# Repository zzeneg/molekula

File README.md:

# molekula: keyboard & framework

## modular framework

This project aims to provide components for building modular ergo keyboards by separating one main PCB into central and side parts. **Side** is a dumb PCB, with key matrix only (up to 25 keys), and accepts all switch types (MX/ChocV1/ChocV2/GLP). **Central** is a keyboard brain, which contains any MCU (wired/wireless/integrated) and additional hardware - encoders/touchpads/trackballs/displays/etc, while keeping its size under 100x100mm. PCBs are interconnected with 12-pin FFC cables, and can be replaced/updated independently.

Such modular approach allows for quick, cheap and easy experimenting with different hardware, prototyping, and reusing of side PCBs.

### PCB examples

- central with pro-micro/nice!nano footprint, nice!view and rotary encoder

- side with 18 keys and minY spacing (19x16mm)

## Molekula keyboards

Reference design using molekula PCBs.

Features:

- minY (19x16mm) spacing
- 36 keys
- wireless
- nice!view support
- rotary encoder

### Molekula2

Unibody that can be disassembled into two parts for traveling

[More info and build guide](./keyboards/Molekula2/README.md)

### Molekula3

Unibody assembled from multiple parts, to allow easy modifications and experiments.

- optimised for FDM printing
- configurable angle and distance between sides (default is 18deg and 60mm)
- different options with dongle or nice!view
- MX/KS-33/ChocV1/ChocV2 are supported, except thumbs are low-profile only

[More info and build guide](./keyboards/Molekula3/README.md)

### minY keycaps

Keycaps designed for minY spacing (19mmx16mm):

- [MX DES](./keycaps/MX-DES-minY/)
- [Choc DES](./keycaps/MX-DES-minY/) - optimised for FDM printing

### Support

If you like my work and want to support my future designs, please consider [sponsorship](https://github.com/sponsors/zzeneg).

### Sponsors

Molekula2 keyboard was sponsored by PCBWay. I can highly recommend their PCBA and 3D printing services - "Imaging Black" resin looks fantastic.

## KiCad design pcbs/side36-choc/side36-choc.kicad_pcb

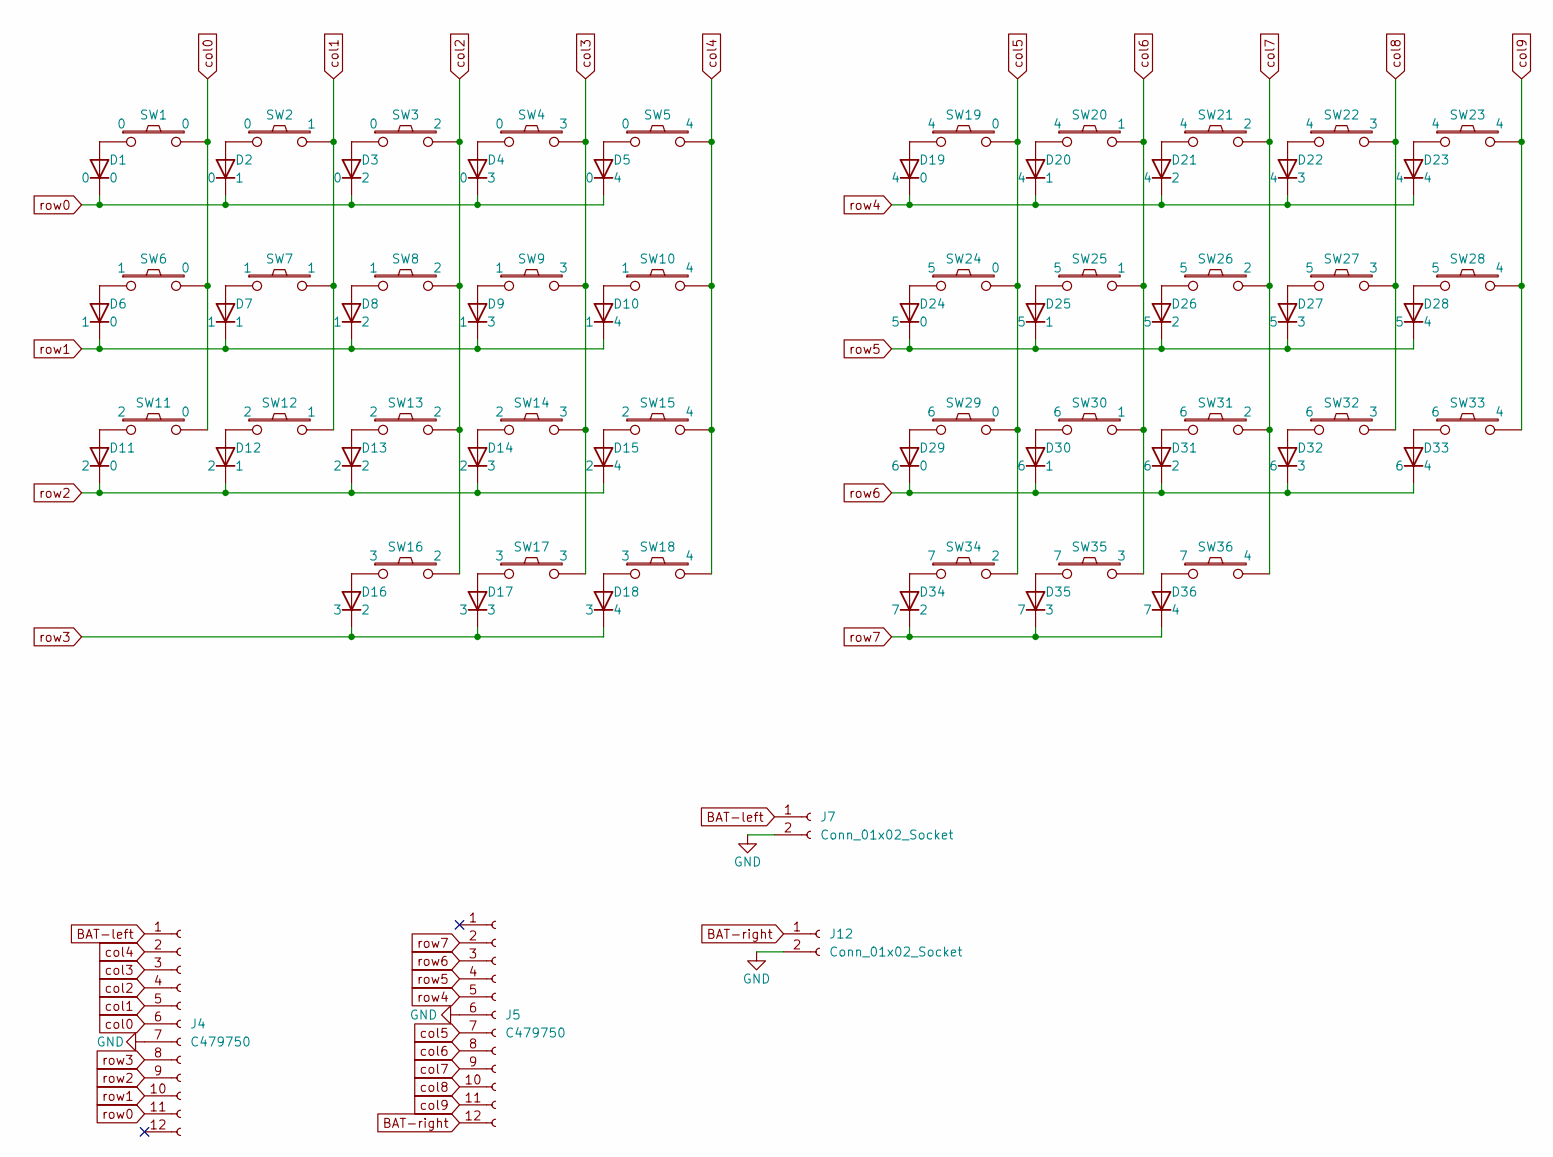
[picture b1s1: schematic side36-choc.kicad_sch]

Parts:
D1, D2, D3, D4, D5, D6, D7, D8, D9, D10, D11, D12, D13, D14, D15, D16, D17, D18, D19, D20, D21, D22, D23, D24, D25, D26, D27, D28, D29, D30, D31, D32, D33, D34, D35, D36: C81598; Diode_1N4148-SOD123
J4, J5: C479750; Connector_FFC-12pin-0.5mm-horizontal
J7, J12: Conn_01x02_Socket; Connector_JST-1x02-2.00mm
SW1, SW2, SW3, SW4, SW5, SW6, SW7, SW8, SW9, SW10, SW11, SW12, SW13, SW14, SW15, SW16, SW17, SW18, SW19, SW20, SW21, SW22, SW23, SW24, SW25, SW26, SW27, SW28, SW29, SW30, SW31, SW32, SW33, SW34, SW35, SW36: Switch; Switch_MXKSChoc-hotswap-choc-spacing

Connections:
BAT-left: J4.1, J7.1
BAT-right: J5.12, J12.1
GND: J4.7, J5.6, J7.2, J12.2
unnamed: D1.2 (A), SW1.1
unnamed: D2.2 (A), SW2.1
unnamed: D3.2 (A), SW3.1
unnamed: D4.2 (A), SW4.1
unnamed: D5.2 (A), SW5.1
unnamed: D6.2 (A), SW6.1
unnamed: D7.2 (A), SW7.1
unnamed: D8.2 (A), SW8.1
unnamed: D9.2 (A), SW9.1
unnamed: D10.2 (A), SW10.1
unnamed: D11.2 (A), SW11.1
unnamed: D12.2 (A), SW12.1
unnamed: D13.2 (A), SW13.1
unnamed: D14.2 (A), SW14.1
unnamed: D15.2 (A), SW15.1
unnamed: D16.2 (A), SW16.1
unnamed: D17.2 (A), SW17.1
unnamed: D18.2 (A), SW18.1
unnamed: D19.2 (A), SW19.1
unnamed: D20.2 (A), SW20.1
unnamed: D21.2 (A), SW21.1
unnamed: D22.2 (A), SW22.1
unnamed: D23.2 (A), SW23.1
unnamed: D24.2 (A), SW24.1
unnamed: D25.2 (A), SW25.1
unnamed: D26.2 (A), SW26.1
unnamed: D27.2 (A), SW27.1
unnamed: D28.2 (A), SW28.1
unnamed: D29.2 (A), SW29.1
unnamed: D30.2 (A), SW30.1
unnamed: D31.2 (A), SW31.1
unnamed: D32.2 (A), SW32.1
unnamed: D33.2 (A), SW33.1
unnamed: D34.2 (A), SW34.1
unnamed: D35.2 (A), SW35.1
unnamed: D36.2 (A), SW36.1
col0: J4.6, SW1.2, SW6.2, SW11.2
col1: J4.5, SW2.2, SW7.2, SW12.2
col2: J4.4, SW3.2, SW8.2, SW13.2, SW16.2
col3: J4.3, SW4.2, SW9.2, SW14.2, SW17.2
col4: J4.2, SW5.2, SW10.2, SW15.2, SW18.2
col5: J5.7, SW19.2, SW24.2, SW29.2, SW34.2
col6: J5.8, SW20.2, SW25.2, SW30.2, SW35.2
col7: J5.9, SW21.2, SW26.2, SW31.2, SW36.2
col8: J5.10, SW22.2, SW27.2, SW32.2
col9: J5.11, SW23.2, SW28.2, SW33.2
row0: D1.1 (K), D2.1 (K), D3.1 (K), D4.1 (K), D5.1 (K), J4.11
row1: D6.1 (K), D7.1 (K), D8.1 (K), D9.1 (K), D10.1 (K), J4.10
row2: D11.1 (K), D12.1 (K), D13.1 (K), D14.1 (K), D15.1 (K), J4.9
row3: D16.1 (K), D17.1 (K), D18.1 (K), J4.8
row4: D19.1 (K), D20.1 (K), D21.1 (K), D22.1 (K), D23.1 (K), J5.5
row5: D24.1 (K), D25.1 (K), D26.1 (K), D27.1 (K), D28.1 (K), J5.4
row6: D29.1 (K), D30.1 (K), D31.1 (K), D32.1 (K), D33.1 (K), J5.3
row7: D34.1 (K), D35.1 (K), D36.1 (K), J5.2

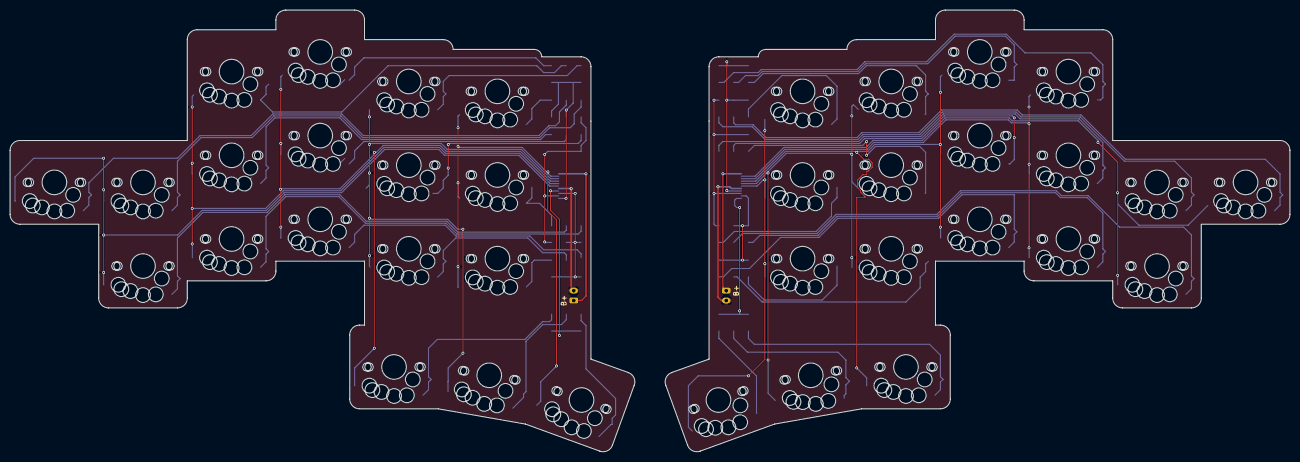
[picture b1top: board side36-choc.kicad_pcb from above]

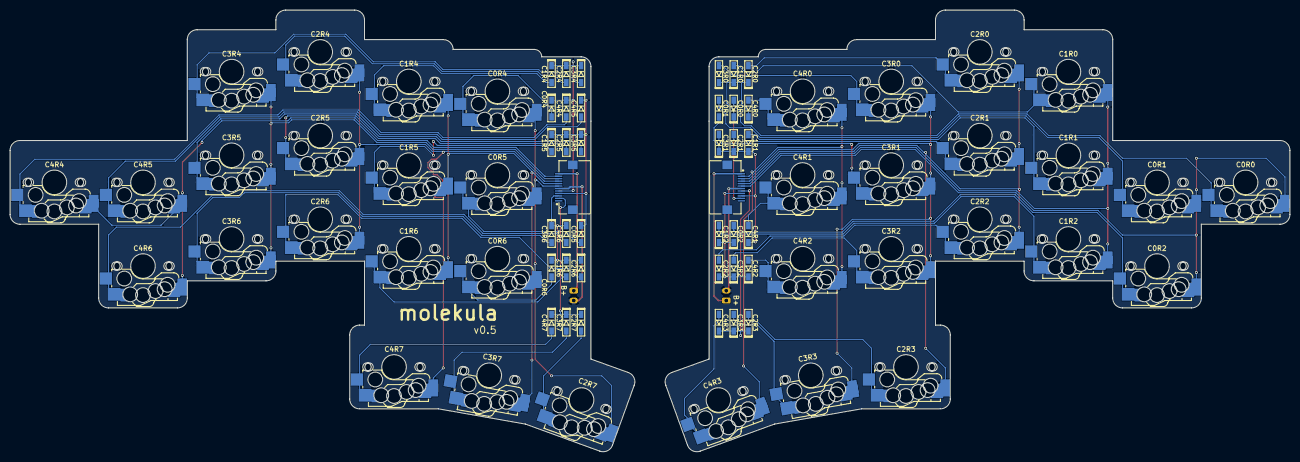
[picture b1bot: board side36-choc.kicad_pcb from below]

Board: 2 copper layers, 260.0 x 89.7 mm, 76 parts (38 on the bottom side), 57 nets.

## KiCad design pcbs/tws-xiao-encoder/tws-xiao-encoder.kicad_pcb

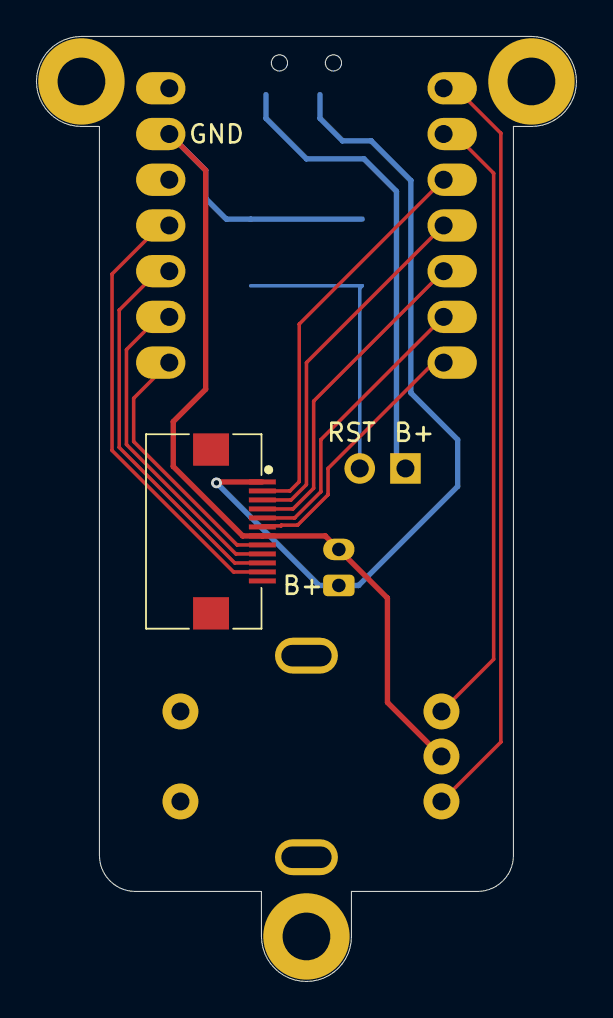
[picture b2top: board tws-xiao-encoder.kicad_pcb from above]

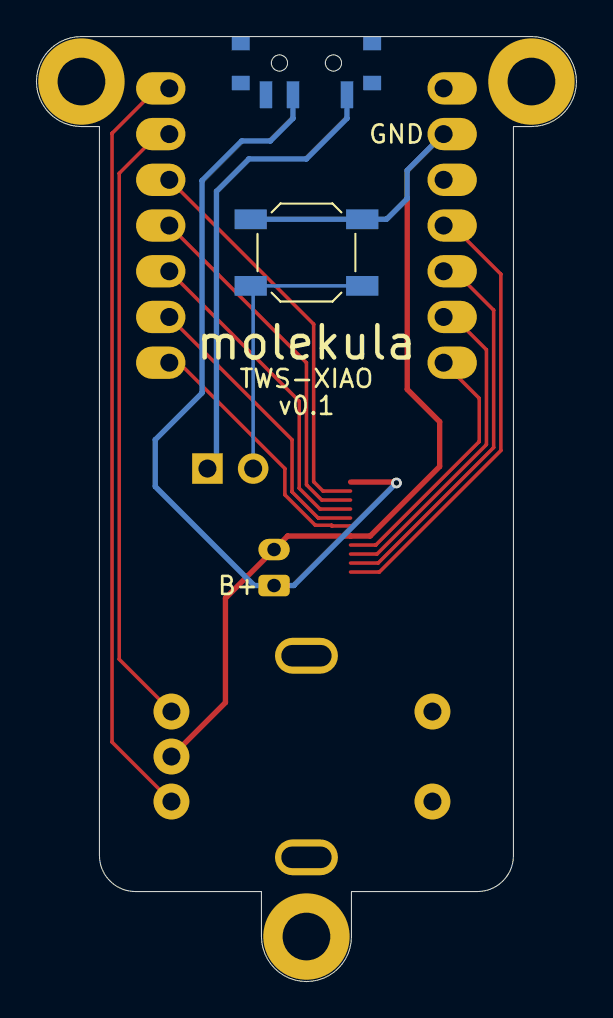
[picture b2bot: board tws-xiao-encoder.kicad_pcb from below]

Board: 2 copper layers, 30.0 x 52.5 mm, 10 parts (3 on the bottom side), 15 nets.

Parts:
H1, H2, H3: MountingHole; Hole_M2-solder-nut-2.5
J2: C479750; Connector_FFC-12pin-0.5mm-horizontal
J3: Conn_01x02_Pin; PinHeader_1x02_P2.54mm_Vertical
J5: Conn_01x02_Socket; Connector_JST-1x02-2.00mm
SW34: SW_SPDT; Switch_SPDT-PCM12
SW37: SW_Push; Button_SW_SPST_SKQG_WithoutStem
SW38: RotaryEncoder_Switch; RotaryEncoder_EC11
U1: MCU_xiao-ble; MCU_xiao-ble-tht

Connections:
BAT: J2.1, J5.1, SW34.2 (B)
BAT-mcu: J3.1, SW34.1 (A)
GND: J2.7, J5.2, SW37.1, SW38.C, U1.13 (GND)
GPIO1: SW38.A, U1.1 (A2/0.02_H)
GPIO2: SW38.B, U1.2 (A4/0.03_H)
RST: J3.2, SW37.2
col0-mcu: J2.6, U1.7 (B8_TX/1.11)
col1-mcu: J2.5, U1.6 (A9_SCL/0.05_H)
col2-mcu: J2.4, U1.5 (A8_SDA/0.04_H)
col3-mcu: J2.3, U1.4 (A11/0.29)
col4-mcu: J2.2, U1.3 (A10/0.28)
row0-mcu: J2.11, U1.11 (A6_MOSI/1.15)
row1-mcu: J2.10, U1.10 (A5_MISO/1.14)
row2-mcu: J2.9, U1.9 (A7_SCK/1.13)
row3-mcu: J2.8, U1.8 (B9_RX/1.12)

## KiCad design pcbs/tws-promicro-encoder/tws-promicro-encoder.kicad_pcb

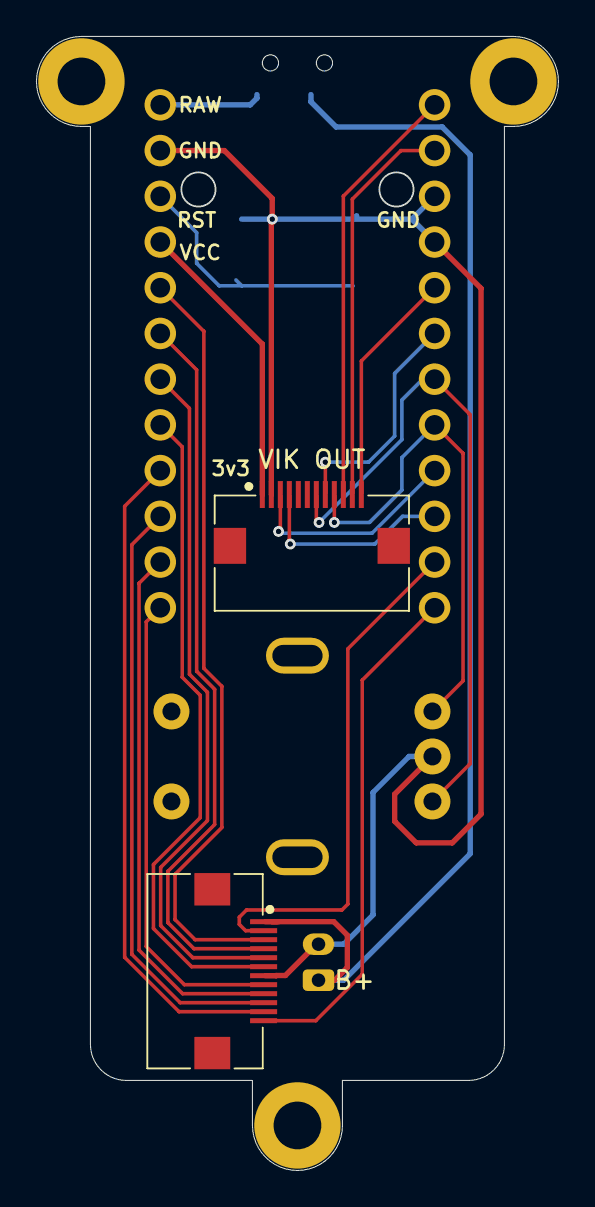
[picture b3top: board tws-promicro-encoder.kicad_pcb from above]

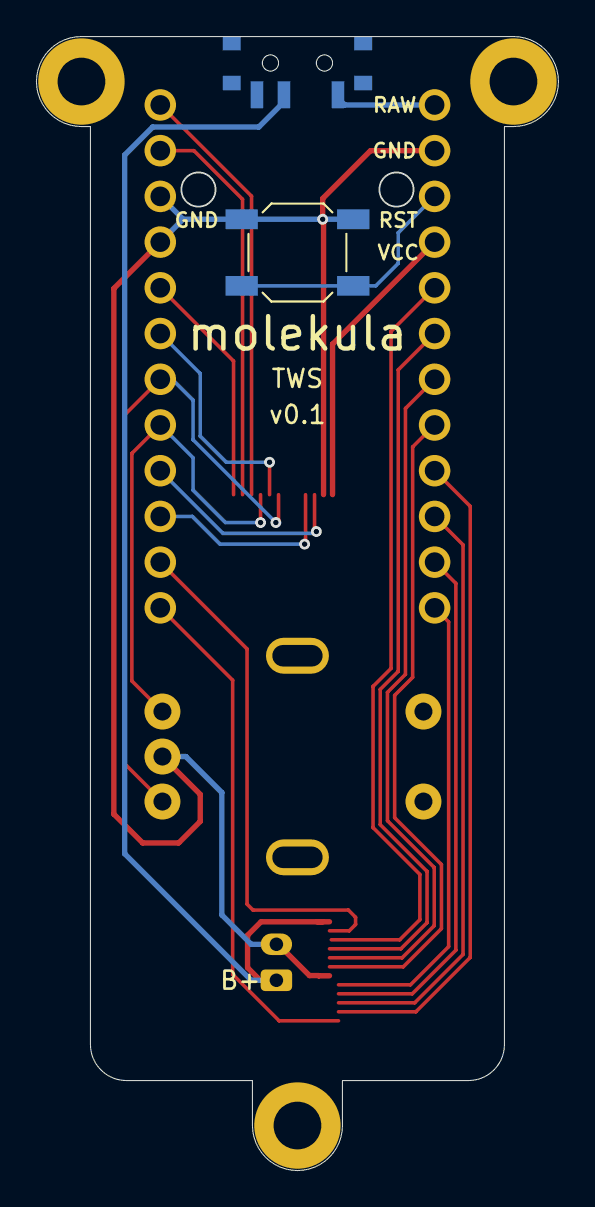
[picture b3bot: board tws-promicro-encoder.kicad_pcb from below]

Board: 2 copper layers, 28.9 x 63.0 mm, 10 parts (3 on the bottom side), 23 nets.

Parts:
H1, H5, H7: MountingHole; Hole_M2-solder-nut-2.5
J1: N!N; MCU_nice-nano
J2: C479750; Connector_FFC-12pin-0.5mm-horizontal
J5: Conn_01x02_Socket; Connector_JST-1x02-2.00mm
SW34: SW_SPDT; Switch_SPDT-PCM12
SW37: SW_Push; Button_SW_SPST_SKQG_WithoutStem
SW38: RotaryEncoder_Switch; RotaryEncoder_EC11
VIK_K1: Connector_VIK-keyboard; Connector_VIK-horizontal-keyboard

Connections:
+3.3V: J1.21 (3V3), VIK_K1.1 (3V3)
BAT: J2.1, J5.1, SW34.2 (B)
BAT-mcu: J1.24 (BAT), SW34.1 (A)
GND: J1.3 (GND), J1.4 (GND), J1.23 (GND), J2.7, J5.2, SW37.1, SW38.C, VIK_K1.2 (GND)
GPIO1: J1.7 (022), SW38.A, VIK_K1.7 (GPIO_AD1)
GPIO2: J1.8 (024), SW38.B, VIK_K1.9 (GPIO_AD2)
MOSI: J1.6 (020), VIK_K1.8 (MOSI)
RST: J1.22 (RST), SW37.2
SCL: J1.10 (011), VIK_K1.4 (SCL)
SDA: J1.9 (100), VIK_K1.3 (SDA)
SPI_CLK: J1.5 (017), VIK_K1.12 (SCLK)
SPI_CS: J1.1 (006), VIK_K1.10 (SPI_CS)
SPI_MISO: J1.2 (008), VIK_K1.11 (MISO)
col0-mcu: J1.17 (115), J2.6
col1-mcu: J1.18 (002), J2.5
col2-mcu: J1.19 (029), J2.4
col3-mcu: J1.20 (031), J2.3
col4-mcu: J1.11 (104), J2.2
free1-mcu: J1.12 (106), J2.12
row0-mcu: J1.16 (113), J2.11
row1-mcu: J1.15 (111), J2.10
row2-mcu: J1.14 (010), J2.9
row3-mcu: J1.13 (009), J2.8

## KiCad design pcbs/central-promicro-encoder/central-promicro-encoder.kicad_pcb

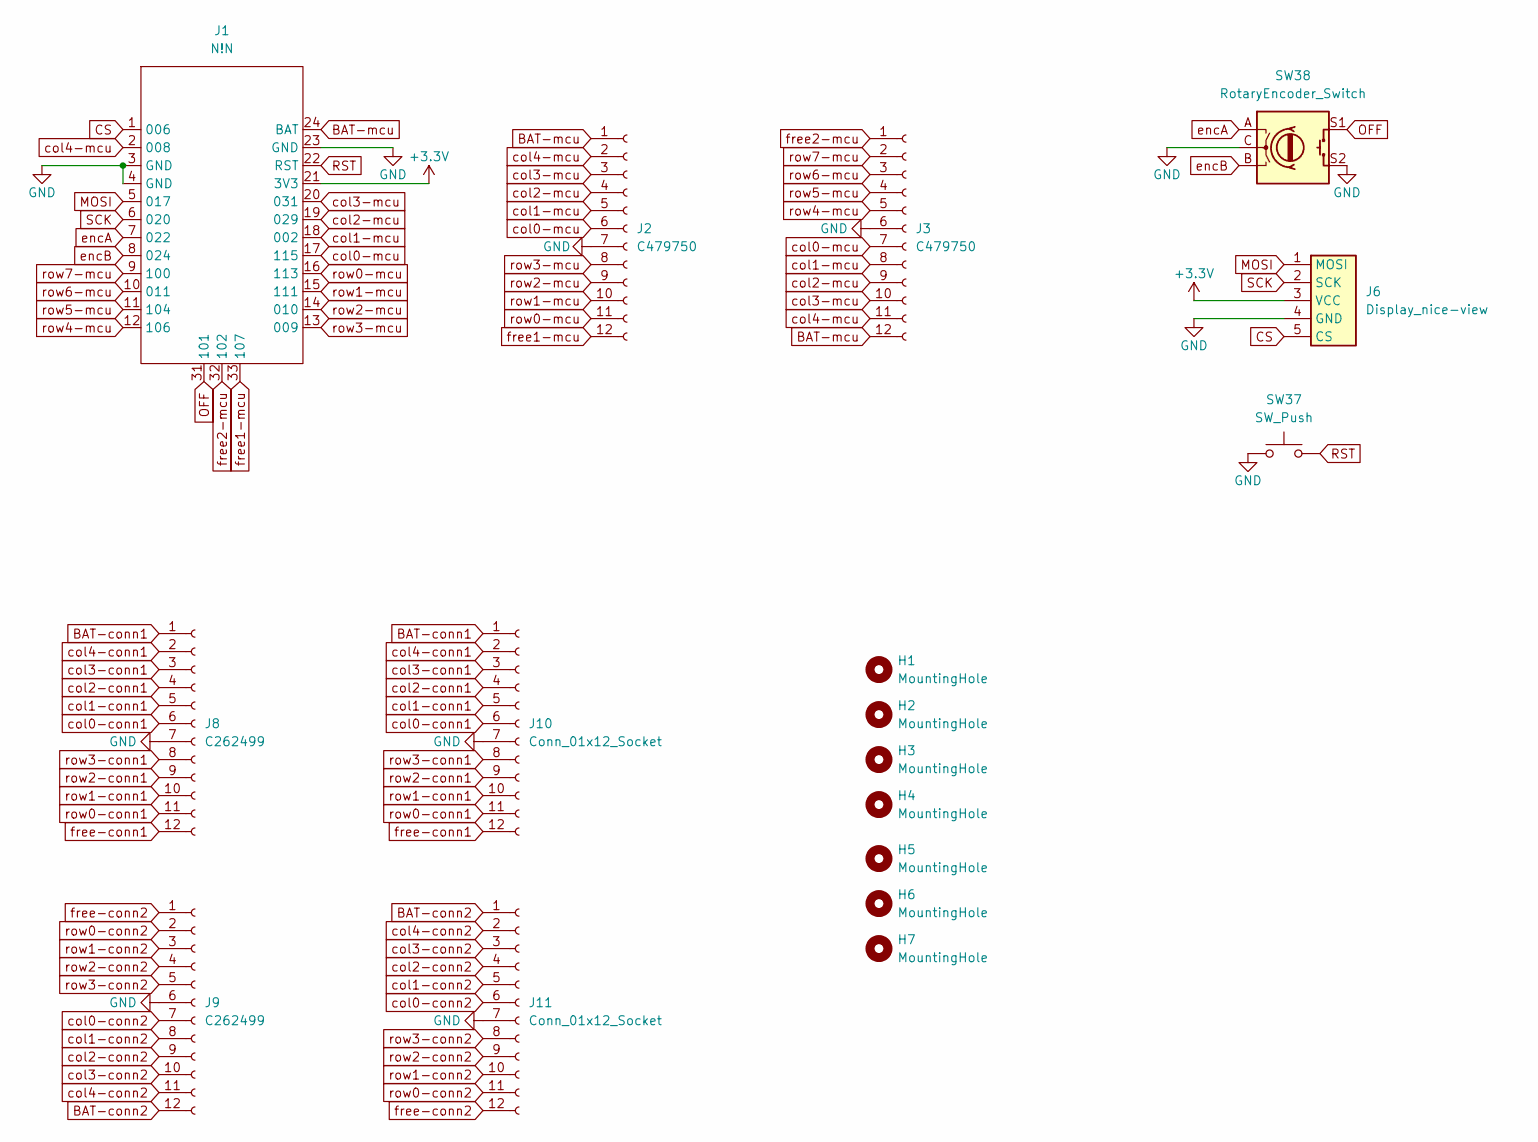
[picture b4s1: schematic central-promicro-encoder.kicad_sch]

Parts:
H1, H2, H3, H4, H5, H6, H7: MountingHole; Hole_M2-solder-nut-2.5
J1: N!N; MCU_nice-nano
J2, J3: C479750; Connector_FFC-12pin-0.5mm-horizontal
J6: Display_nice-view
J8, J9: C262499; Connector_FFC-12pin-0.5mm-vertical
J10, J11: Conn_01x12_Socket; Connector_Magnetic-12pin
SW37: SW_Push; Button_SW_SPST_SKQG_WithoutStem
SW38: RotaryEncoder_Switch; RotaryEncoder_EC11

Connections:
+3.3V: J1.21 (3V3), J6.3 (VCC)
BAT-conn1: J8.1, J10.1
BAT-conn2: J9.12, J11.1
BAT-mcu: J1.24 (BAT), J2.1, J3.12
CS: J1.1 (006), J6.5 (CS)
GND: J1.3 (GND), J1.4 (GND), J1.23 (GND), J2.7, J3.6, J6.4 (GND), J8.7, J9.6, J10.7, J11.7, SW37.1, SW38.C, SW38.S2
MOSI: J1.5 (017), J6.1 (MOSI)
OFF: J1.31 (101), SW38.S1
RST: J1.22 (RST), SW37.2
SCK: J1.6 (020), J6.2 (SCK)
col0-conn1: J8.6, J10.6
col0-conn2: J9.7, J11.6
col0-mcu: J1.17 (115), J2.6, J3.7
col1-conn1: J8.5, J10.5
col1-conn2: J9.8, J11.5
col1-mcu: J1.18 (002), J2.5, J3.8
col2-conn1: J8.4, J10.4
col2-conn2: J9.9, J11.4
col2-mcu: J1.19 (029), J2.4, J3.9
col3-conn1: J8.3, J10.3
col3-conn2: J9.10, J11.3
col3-mcu: J1.20 (031), J2.3, J3.10
col4-conn1: J8.2, J10.2
col4-conn2: J9.11, J11.2
col4-mcu: J1.2 (008), J2.2, J3.11
encA: J1.7 (022), SW38.A
encB: J1.8 (024), SW38.B
free1-mcu: J1.33 (107), J2.12
free2-mcu: J1.32 (102), J3.1
free-conn1: J8.12, J10.12
free-conn2: J9.1, J11.12
row0-conn1: J8.11, J10.11
row0-conn2: J9.2, J11.11
row0-mcu: J1.16 (113), J2.11
row1-conn1: J8.10, J10.10
row1-conn2: J9.3, J11.10
row1-mcu: J1.15 (111), J2.10
row2-conn1: J8.9, J10.9
row2-conn2: J9.4, J11.9
row2-mcu: J1.14 (010), J2.9
row3-conn1: J8.8, J10.8
row3-conn2: J9.5, J11.8
row3-mcu: J1.13 (009), J2.8
row4-mcu: J1.12 (106), J3.5
row5-mcu: J1.11 (104), J3.4
row6-mcu: J1.10 (011), J3.3
row7-mcu: J1.9 (100), J3.2

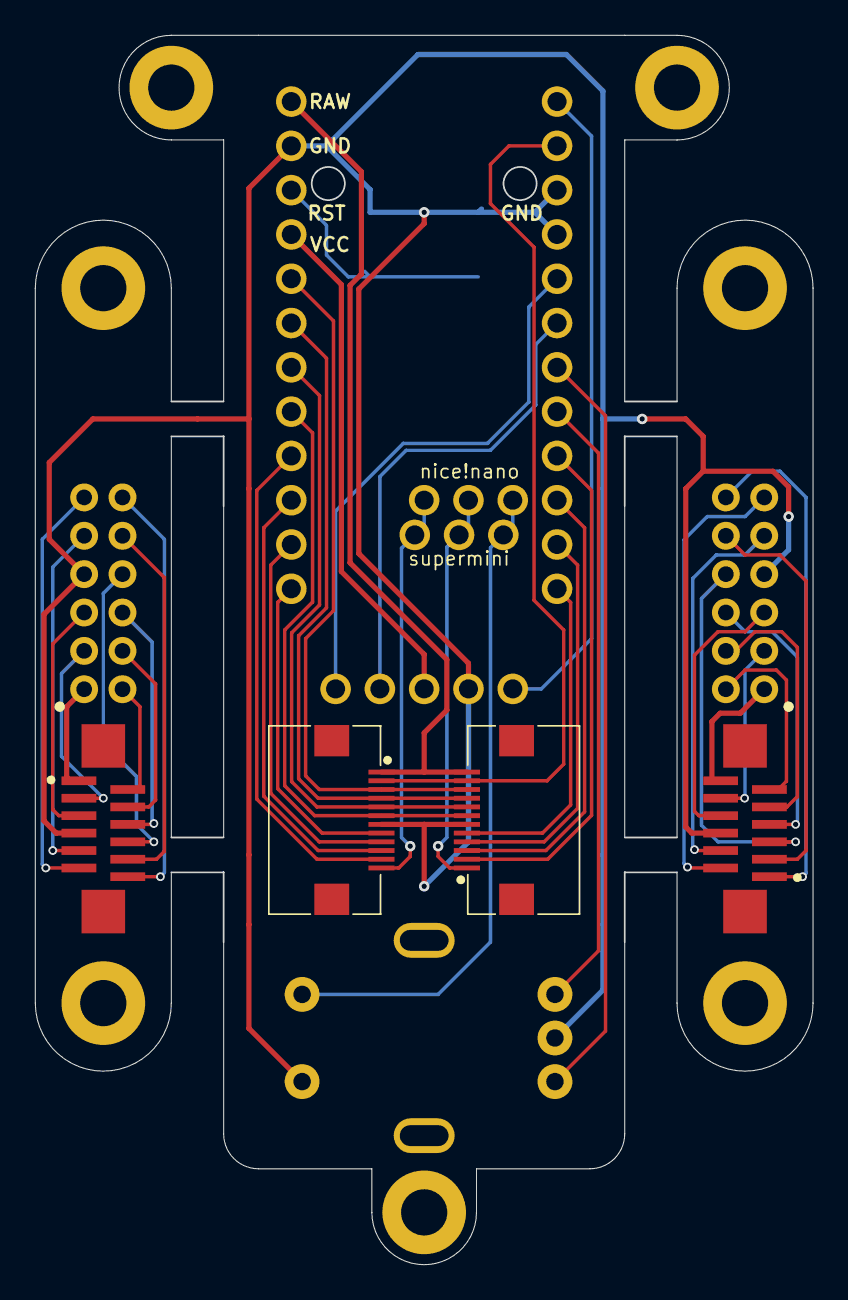
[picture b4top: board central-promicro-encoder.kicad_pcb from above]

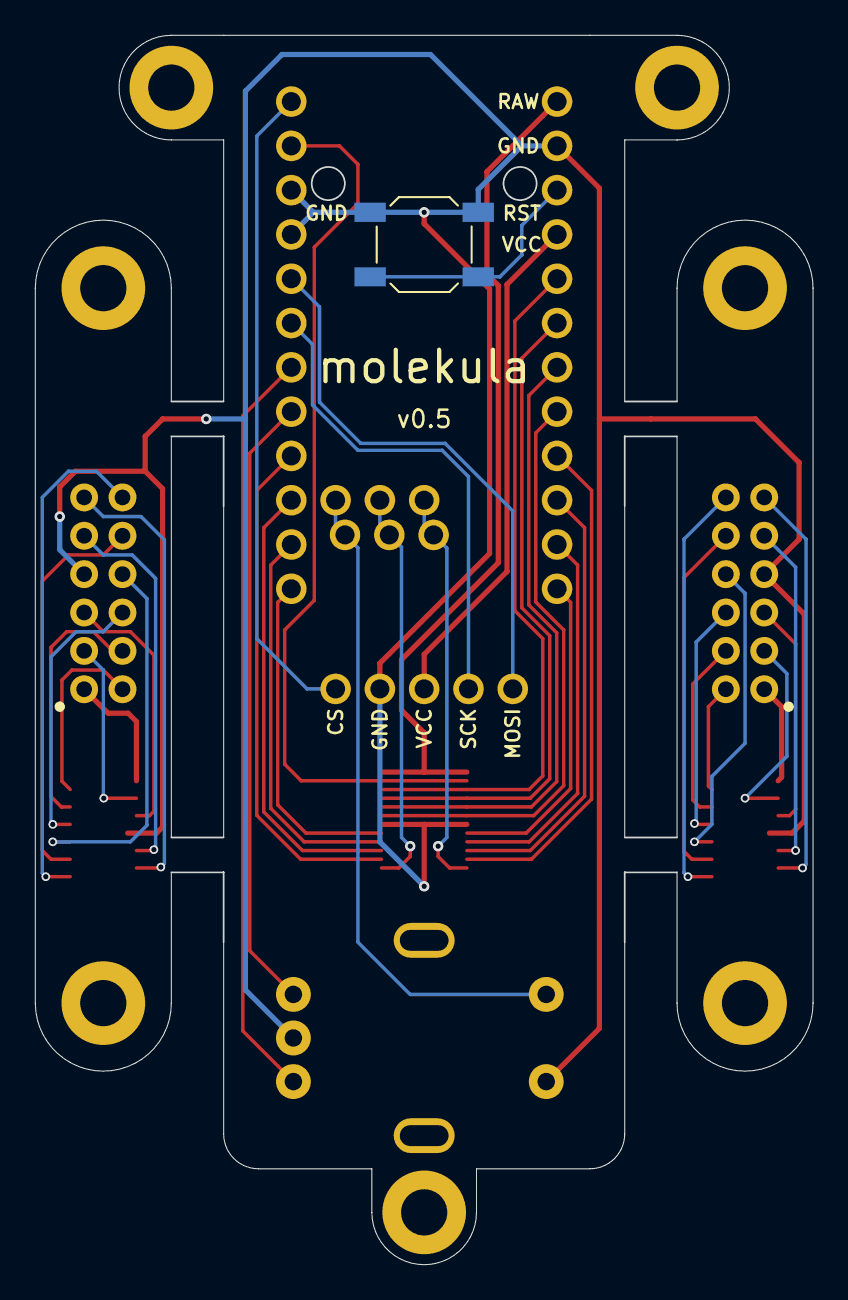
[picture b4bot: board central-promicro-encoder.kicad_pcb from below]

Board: 2 copper layers, 44.5 x 70.5 mm, 17 parts (3 on the bottom side), 47 nets.

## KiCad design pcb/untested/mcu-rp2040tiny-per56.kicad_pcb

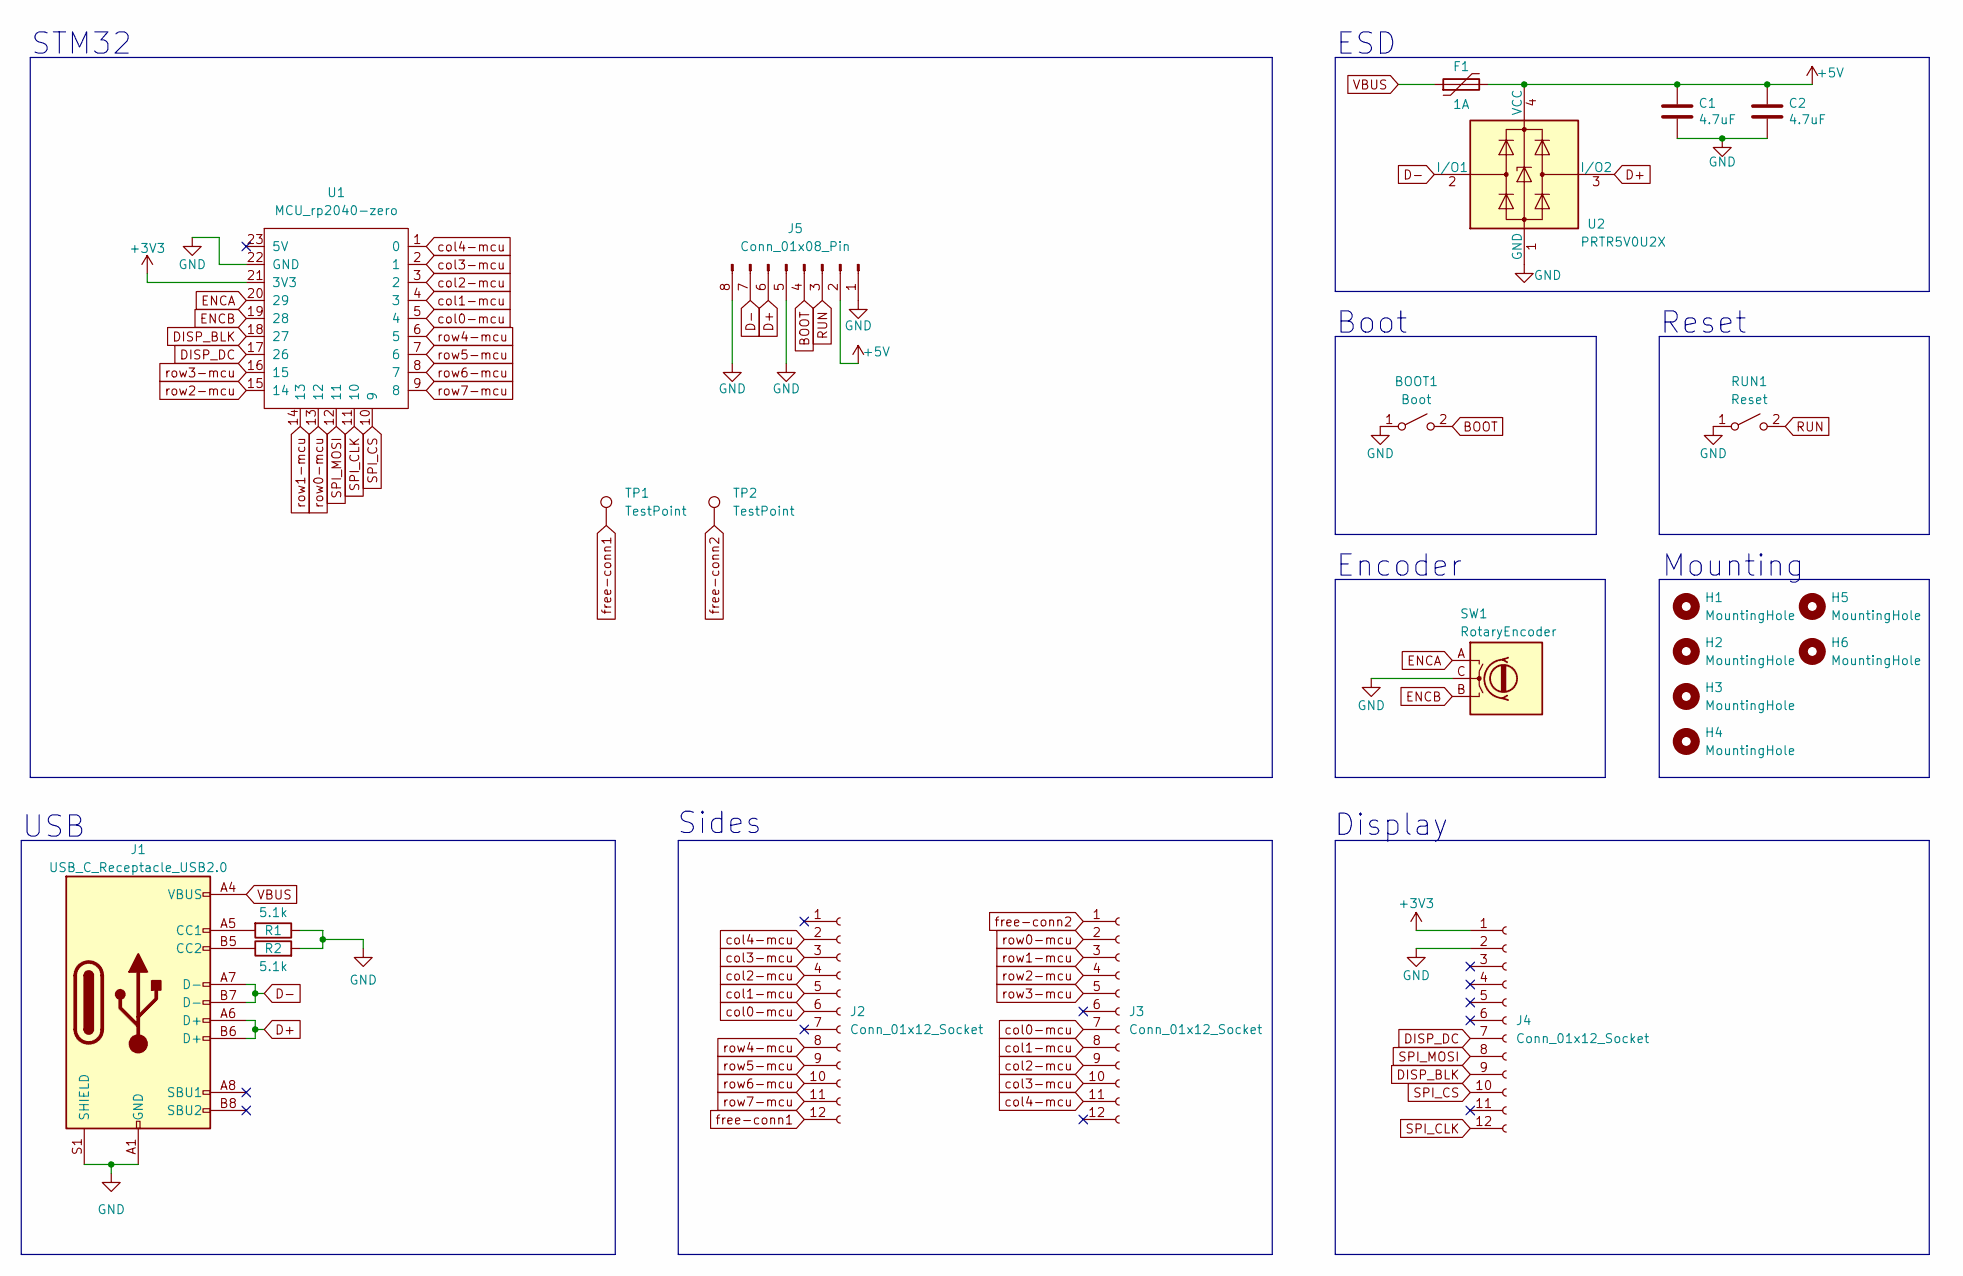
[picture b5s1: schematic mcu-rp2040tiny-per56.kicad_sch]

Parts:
BOOT1: Boot; SW_SPST_TL3342
C1, C2: 4.7uF; C_1206_3216Metric; LCSC C307331
F1: 1A; Fuse_1206_3216Metric; LCSC C135341
H1, H2, H3, H4: MountingHole; Hole_M2-solder-nut-2.5
H5, H6: MountingHole; Hole_M2
J1: USB_C_Receptacle_USB2.0; Connector_USB-C-31-M-12; JlcRotOffset 180
J2, J3: Conn_01x12_Socket; Connector_FFC-12pin-0.5mm-horizontal
J4: Conn_01x12_Socket; Connector_VIK-horizontal-keyboard
J5: Conn_01x08_Pin; Hirose_FH12-8S-0.5SH_1x08-1MP_P0.50mm_Horizontal
R1, R2: 5.1k; R_0805_2012Metric
RUN1: Reset; SW_SPST_TL3342
SW1: RotaryEncoder; RingEncoder_PER561P115N0015
TP1, TP2: TestPoint; TestPoint_Pad_D1.5mm
U1: MCU_rp2040-zero; MCU_rp2040-tiny-tht
U2: PRTR5V0U2X; SOT-143; LCSC C2827688

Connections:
+3V3: J4.1, U1.21 (3V3)
+5V: C1.1, C2.1, F1.2, J5.2, U2.4 (VCC)
BOOT: BOOT1.2 (B), J5.4
D+: J1.A6 (D+), J1.B6 (D+), J5.6, U2.3 (I/O2)
D-: J1.A7 (D-), J1.B7 (D-), J5.7, U2.2 (I/O1)
DISP_BLK: J4.9, U1.18 (27)
DISP_DC: J4.7, U1.17 (26)
ENCA: SW1.A, U1.20 (29)
ENCB: SW1.B, U1.19 (28)
GND: BOOT1.1 (A), C1.2, C2.2, J1.A1 (GND), J1.A12 (GND), J1.B1 (GND), J1.B12 (GND), J1.S1 (SHIELD), J4.2, J5.1, J5.5, J5.8, R1.1, R2.2, RUN1.1 (A), SW1.C, U1.22 (GND), U2.1 (GND)
unnamed: J1.A5 (CC1), R1.2
unnamed: J1.B5 (CC2), R2.1
RUN: J5.3, RUN1.2 (B)
SPI_CLK: J4.12, U1.11 (10)
SPI_CS: J4.10, U1.10 (9)
SPI_MOSI: J4.8, U1.12 (11)
VBUS: F1.1, J1.A4 (VBUS), J1.A9 (VBUS), J1.B4 (VBUS), J1.B9 (VBUS)
col0-mcu: J2.6, J3.7, U1.5 (4)
col1-mcu: J2.5, J3.8, U1.4 (3)
col2-mcu: J2.4, J3.9, U1.3 (2)
col3-mcu: J2.3, J3.10, U1.2 (1)
col4-mcu: J2.2, J3.11, U1.1 (0)
free-conn1: J2.12, TP1.1
free-conn2: J3.1, TP2.1
row0-mcu: J3.2, U1.13 (12)
row1-mcu: J3.3, U1.14 (13)
row2-mcu: J3.4, U1.15 (14)
row3-mcu: J3.5, U1.16 (15)
row4-mcu: J2.8, U1.6 (5)
row5-mcu: J2.9, U1.7 (6)
row6-mcu: J2.10, U1.8 (7)
row7-mcu: J2.11, U1.9 (8)

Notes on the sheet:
USB
Boot
Reset
Encoder
Sides
Display
ESD
Mounting
STM32

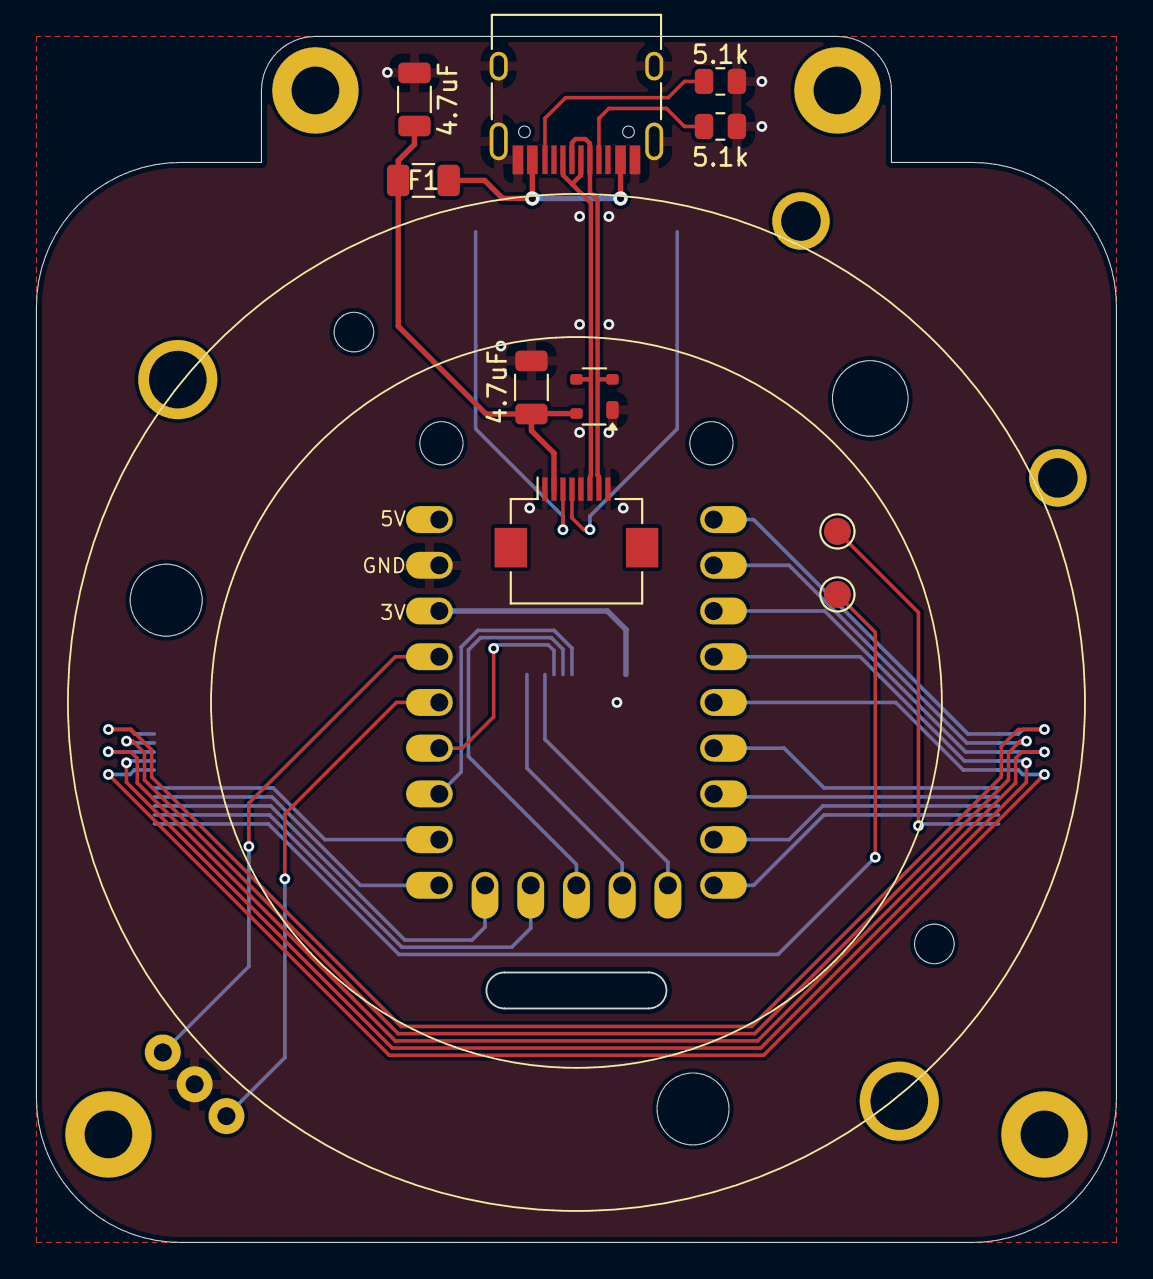
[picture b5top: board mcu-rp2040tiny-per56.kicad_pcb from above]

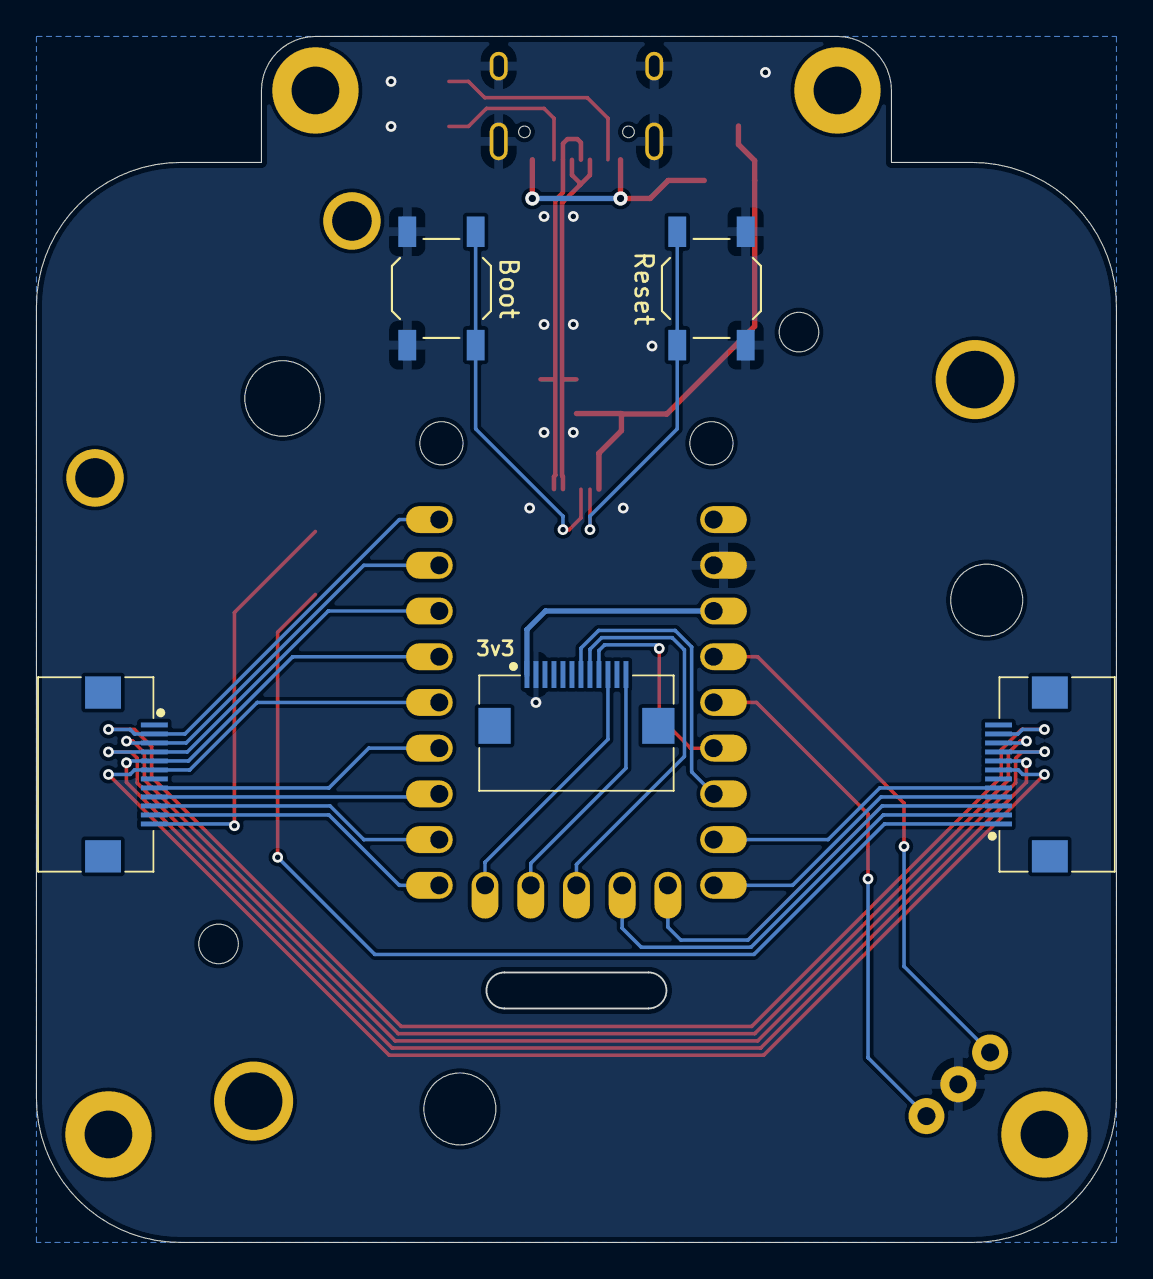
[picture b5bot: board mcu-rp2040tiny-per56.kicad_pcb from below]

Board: 2 copper layers, 60.0 x 67.0 mm, 23 parts (5 on the bottom side), 32 nets.
